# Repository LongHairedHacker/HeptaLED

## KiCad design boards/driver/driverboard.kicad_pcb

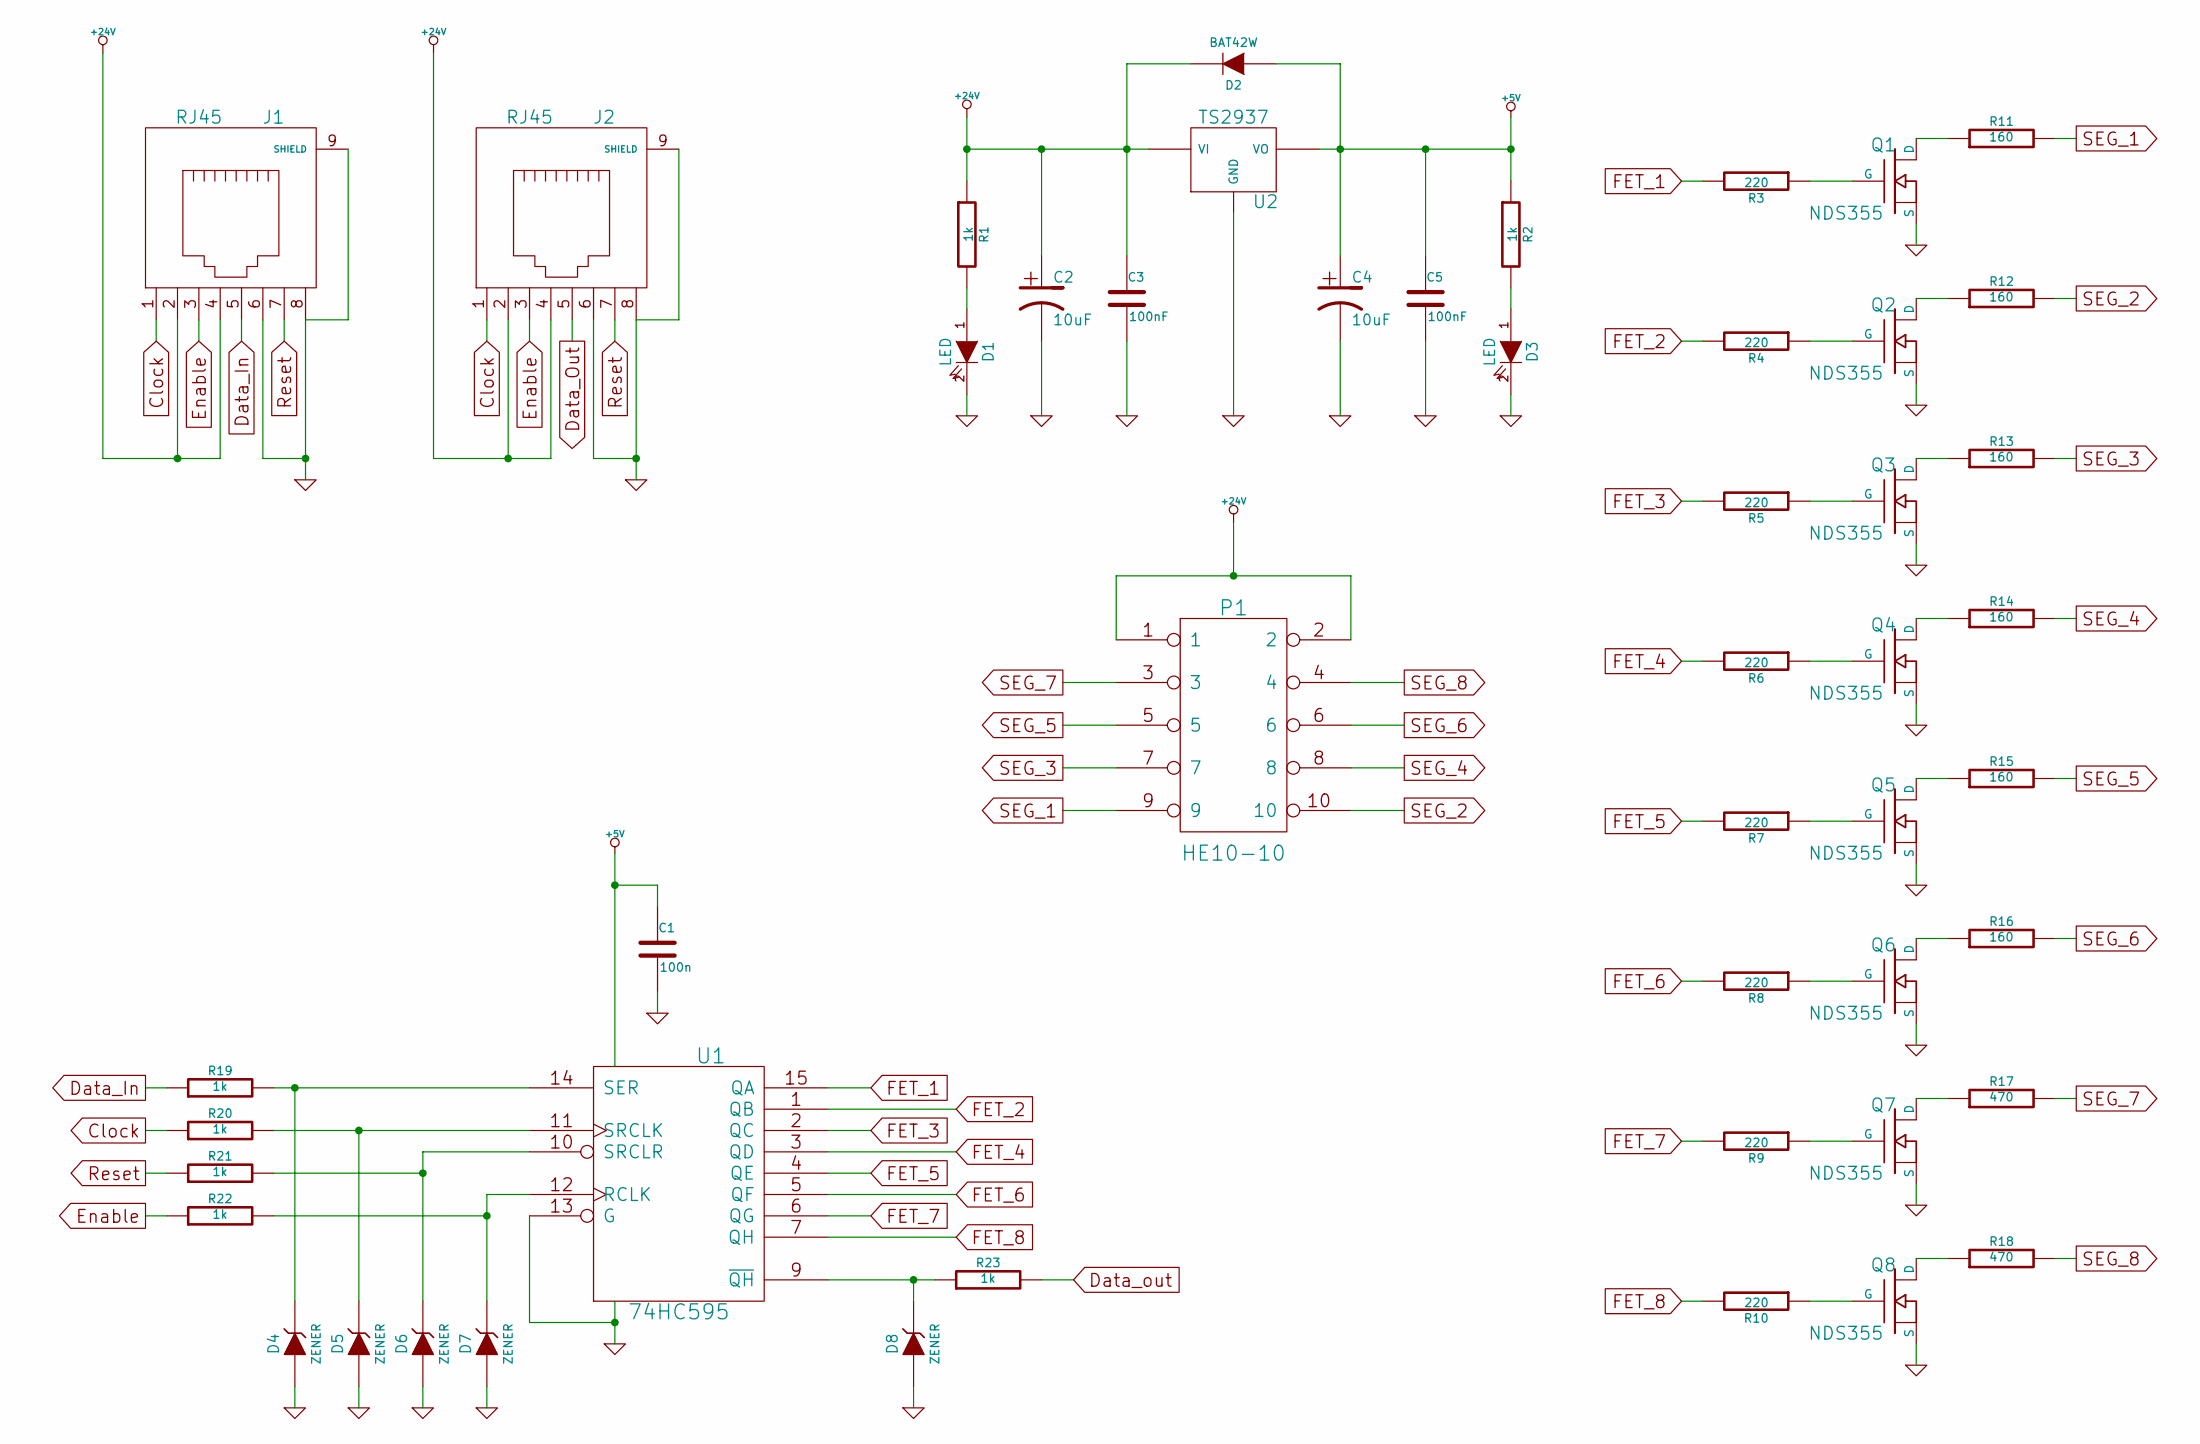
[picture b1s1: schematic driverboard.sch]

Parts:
C1: 100n
C2, C4: 10uF
C3, C5: 100nF
D1, D3: LED
D2: BAT42W
D4, D5, D6, D7, D8: ZENER
J1, J2: RJ45
P1: HE10-10
Q1, Q2, Q3, Q4, Q5, Q6, Q7, Q8: NDS355
R1, R2, R19, R20, R21, R22, R23: 1k
R3, R4, R5, R6, R7, R8, R9, R10: 220
R11, R12, R13, R14, R15, R16: 160
R17, R18: 470
U1: 74HC595
U2: TS2937

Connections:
+5V: C1.1, C4.1, C5.1, D2.1 (A), R2.1, U1.16 (VCC), U2.3 (VO)
+24V: C2.1, C3.1, D2.2 (K), J1.2, J1.4, J2.2, J2.4, P1.1, P1.2, R1.1, U2.1 (VI)
Clock: J1.1, J2.1, R20.1
Data_In: J1.5, R19.1
Data_Out: J2.5, R23.2
Enable: J1.3, J2.3, R22.1
FET_1: R3.2, U1.15 (QA)
FET_2: R4.2, U1.1 (QB)
FET_3: R5.2, U1.2 (QC)
FET_4: R6.2, U1.3 (QD)
FET_5: R7.2, U1.4 (QE)
FET_6: R8.2, U1.5 (QF)
FET_7: R9.2, U1.6 (QG)
FET_8: R10.2, U1.7 (QH)
GND: C1.2, C2.2, C3.2, C4.2, C5.2, D1.2 (K), D3.2 (K), D4.1 (A), D5.1 (A), D6.1 (A), D7.1 (A), D8.1 (A), J1.6, J1.8, J1.9 (SHIELD), J2.6, J2.8, J2.9 (SHIELD), Q1.3 (S), Q2.3 (S), Q3.3 (S), Q4.3 (S), Q5.3 (S), Q6.3 (S), Q7.3 (S), Q8.3 (S), U1.8 (GND), U1.13 (G), U2.2 (GND)
unnamed: Q4.2 (D), R14.1
unnamed: Q4.1 (G), R6.1
unnamed: Q3.2 (D), R13.1
unnamed: Q3.1 (G), R5.1
unnamed: Q2.1 (G), R4.1
unnamed: Q1.2 (D), R11.1
unnamed: Q1.1 (G), R3.1
unnamed: Q2.2 (D), R12.1
unnamed: Q5.2 (D), R15.1
unnamed: Q5.1 (G), R7.1
unnamed: Q6.2 (D), R16.1
unnamed: D6.2 (K), R21.2, U1.10 (SRCLR)
unnamed: D5.2 (K), R20.2, U1.11 (SRCLK)
unnamed: D8.2 (K), R23.1, U1.9 (~QH)
unnamed: D4.2 (K), R19.2, U1.14 (SER)
unnamed: D7.2 (K), R22.2, U1.12 (RCLK)
unnamed: Q8.2 (D), R18.1
unnamed: Q8.1 (G), R10.1
unnamed: Q7.2 (D), R17.1
unnamed: Q7.1 (G), R9.1
unnamed: Q6.1 (G), R8.1
unnamed: D3.1 (A), R2.2
unnamed: D1.1 (A), R1.2
Reset: J1.7, J2.7, R21.1
SEG_1: P1.9, R11.2
SEG_2: P1.10, R12.2
SEG_3: P1.7, R13.2
SEG_4: P1.8, R14.2
SEG_5: P1.5, R15.2
SEG_6: P1.6, R16.2
SEG_7: P1.3, R17.2
SEG_8: P1.4, R18.2

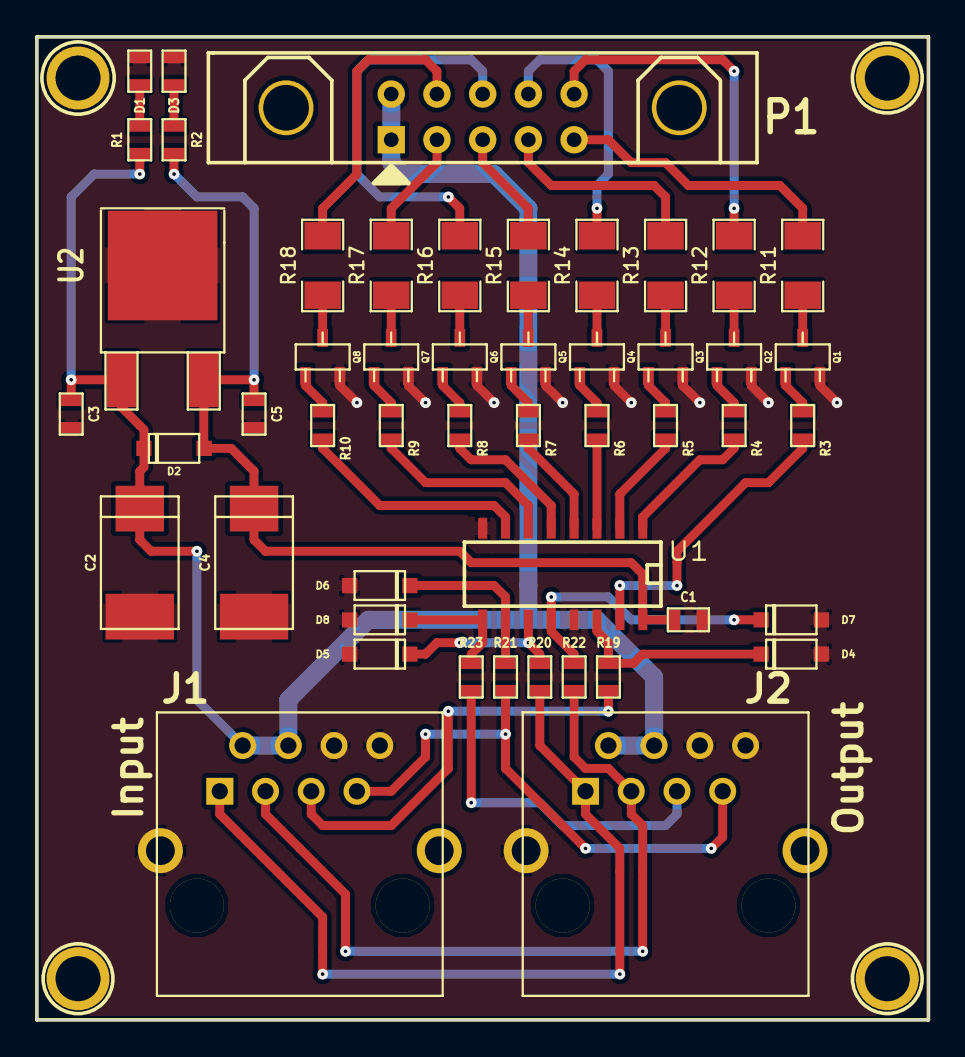
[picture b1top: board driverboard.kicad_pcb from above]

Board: 2 copper layers, 49.5 x 54.6 mm, 53 parts (0 on the bottom side), 47 nets.

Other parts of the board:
1PIN, 1PIN#2, 1PIN#3, 1PIN#4: P***; 1pin

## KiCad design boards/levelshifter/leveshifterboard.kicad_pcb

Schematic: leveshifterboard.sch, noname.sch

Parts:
C1, C2, C4, C6, C7: 100nF
C3, C5: 10uF
D1, D2, D4: LED
D3: BAT42W
D5, D6, D7, D8: ZENER_5.6V
F1: FUSE
J1: RJ45
P1: CONN_2
P2: CONN_7
Q1: IRLR110
Q2: NDS355
R1: 10k
R2: 90k
R3, R6, R7, R8, R9, R10, R11, R12, R13, R14, R15, R16: 1k
R4: 100k
R5: 0.05
RV1: POT
SW1: SW_PUSH
U1: LM358
U2: SN74LVC1G74
U3: 74HCT125
U4: TS2937

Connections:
3.3_Clock: P2.2, U3.2 (1A)
3.3_Data_Out: P2.3, U3.9 (3A)
3.3_Enable: P2.4, U3.5 (2A)
3.3_Reset: P2.5, U3.12 (4A)
+3.3V: P2.1, R12.1
+5V: C2.1, C5.1, C6.1, C7.1, D3.1 (A), R3.1, R6.1, R8.2, R10.1, RV1.1, U1.8 (V+), U2.14, U3.14 (Vcc), U4.3 (VO)
+24V: C3.1, C4.1, D3.2 (K), F1.2, R9.1, U4.1 (VI); also elsewhere on the board
BusOff: R7.1, R11.1, U2.5, U3.1 (OE1), U3.4 (OE2), U3.10 (OE3), U3.13 (OE4)
Clock: J1.1, R13.2
Data_Out: J1.5, R15.2
Enable: J1.3, R14.2
GND: C1.2, C2.2, C3.2, C4.2, C5.2, C6.2, C7.2, D1.2 (K), D2.2 (K), D4.2 (K), D5.1 (A), D6.1 (A), D7.1 (A), D8.1 (A), P1.1, P2.7, Q2.3 (S), R1.2, R5.2, RV1.3, SW1.2, U1.4 (V-), U2.2, U2.3, U2.7, U3.7 (GND), U4.2 (GND); also elsewhere on the board
unnamed: C1.1, R4.2, U1.6 (-)
unnamed: P2.6, Q2.2 (D), R12.2
unnamed: D1.1 (A), R7.2
unnamed: R8.1, SW1.1, U2.1
unnamed: D8.2 (K), R16.1, U3.11 (Y4)
unnamed: D7.2 (K), R15.1, U3.8 (Y3)
unnamed: D6.2 (K), R14.1, U3.6 (Y2)
unnamed: D5.2 (K), R13.1, U3.3 (Y1)
unnamed: Q2.1 (G), R11.2
unnamed: RV1.2, U1.5 (+)
unnamed: R2.2, R4.1, U1.1
unnamed: F1.1, P1.2 (PM)
unnamed: D4.1 (A), R10.2
unnamed 25: J1.2, J1.4; also elsewhere on the board
unnamed: D2.1 (A), R9.2
unnamed: R1.1, R2.1, U1.2 (-)
PowerOn: R3.2, U2.6; also elsewhere on the board
Reset: J1.7, R16.2
Sense: J1.6, J1.8, J1.9 (SHIELD), R5.1, U1.3 (+)
Shutdown: R6.2, U1.7, U2.4

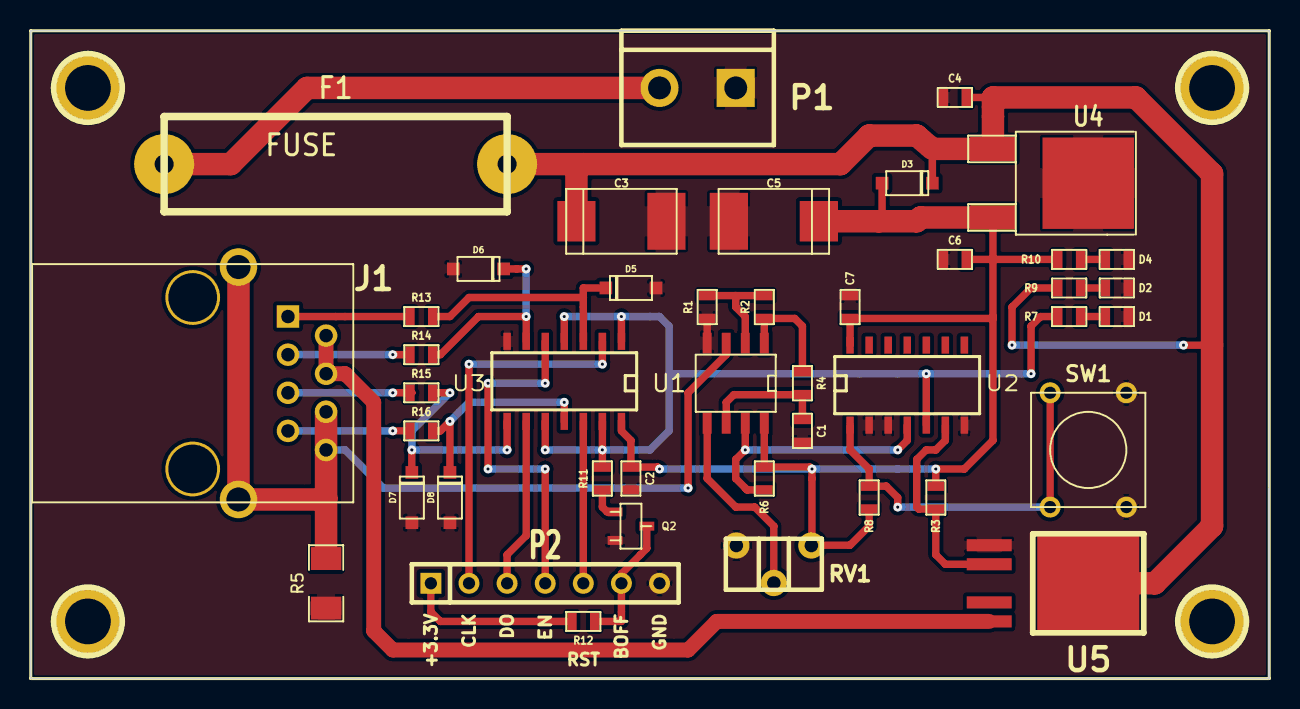
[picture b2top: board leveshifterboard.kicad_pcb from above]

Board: 2 copper layers, 82.5 x 43.2 mm, 47 parts (0 on the bottom side), 32 nets.

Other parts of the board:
1PIN, 1PIN#2, 1PIN#3, 1PIN#4: P***; 1pin
U5: BTS462; TO252-5L

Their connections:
+24V: U5.3; also elsewhere on the board
GND: U5.1; also elsewhere on the board
unnamed 25: U5.5; also elsewhere on the board
PowerOn: U5.2; also elsewhere on the board

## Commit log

2014-01-28 First version of board
2014-01-29 Cleaned up silkscreen
2014-02-16 Added holes to driver board
2014-02-16 Added cad for enclosures
2014-02-17 Better folder structure
2014-02-26 First levelshifter schematic
2014-02-26 Swicthed to integrated level shifter
2014-03-16 First version of levelshifter board
2014-03-23 Semifinal version of enclosure lids
2014-05-01 Small update on driverboard
2014-05-01 Fixed silkscreen
2014-05-01 Final version 1.0
2014-05-01 Generate files for fabrication
2014-05-24 Added devicetree overlay
2014-07-31 Added drawings for display
2014-08-17 Started fixing schematics
2014-08-19 Updated driverboard layout
2014-08-23 Updated levelshifter schematic
2014-09-04 More work on levelshifter
2014-09-18 Fixed levelshifter board
2014-09-18 Minor Silkscreen fixes
2014-10-21 Final fixes to board layouts
2014-10-21 Updated gerbers and postscripts
2014-10-21 Updated version number
2014-10-21 Panelized boards
2014-10-22 Added logos
2014-10-22 Fixed production files
2014-11-19 Added libheptaled
2014-11-21 Updated resistor values
2014-12-16 Adjusted padsizes for stencil
